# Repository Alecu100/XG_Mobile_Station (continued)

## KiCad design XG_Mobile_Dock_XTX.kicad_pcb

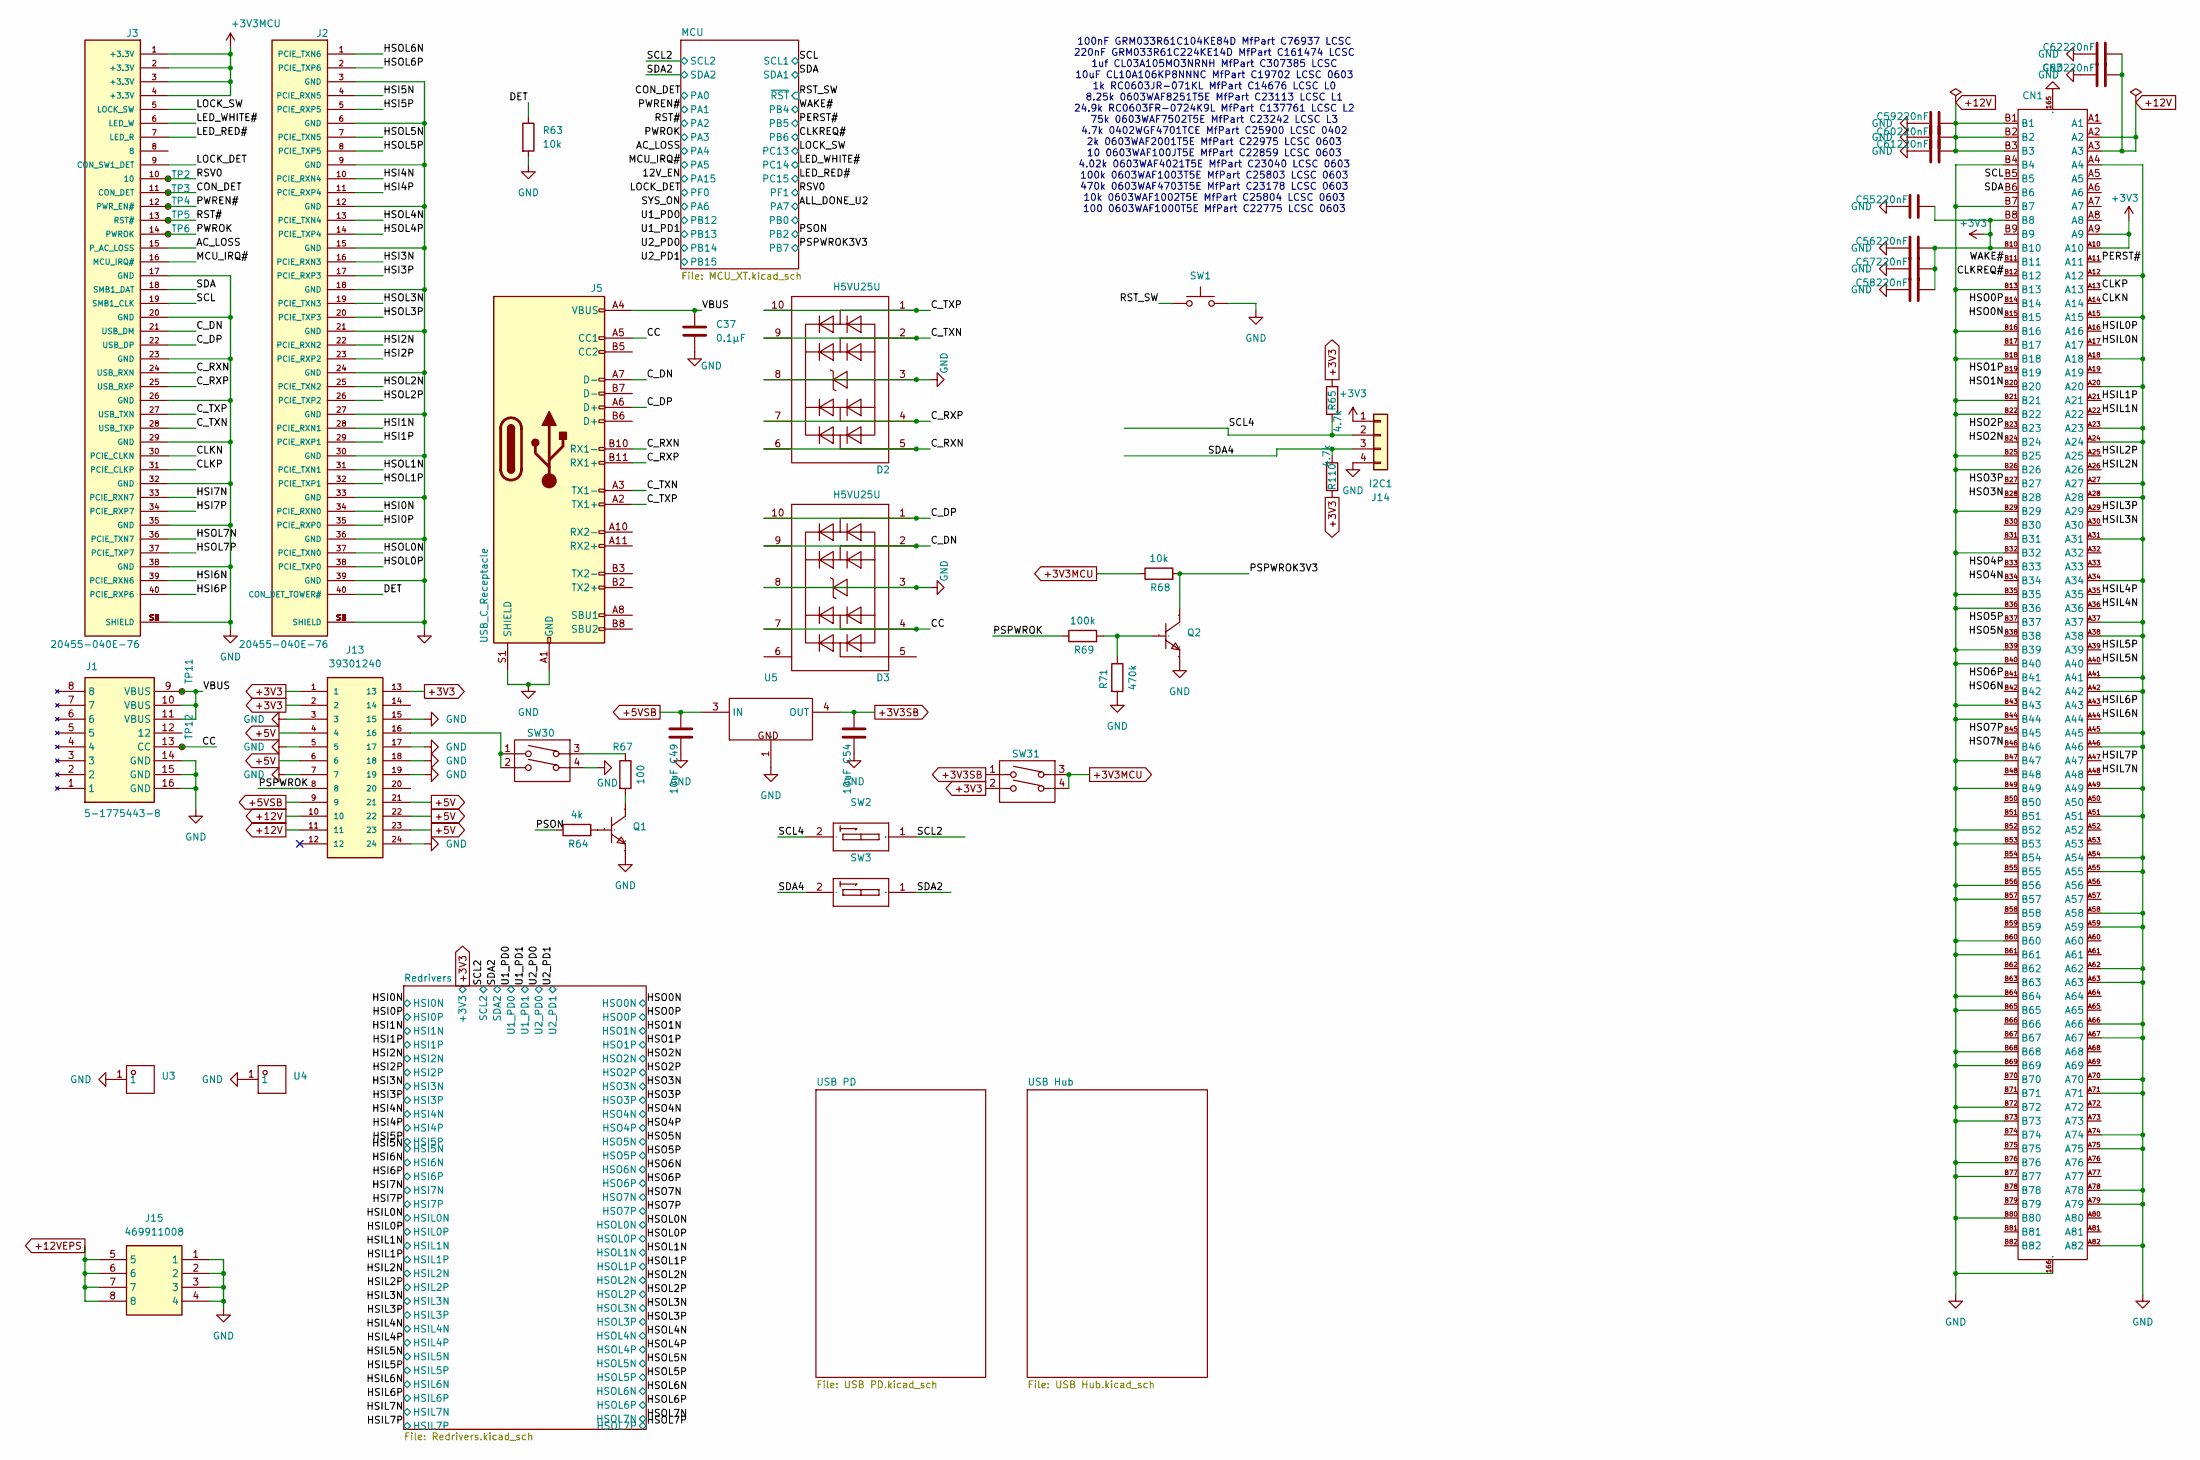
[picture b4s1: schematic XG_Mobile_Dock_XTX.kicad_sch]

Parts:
C37: 0.1μF; C_0402_1005Metric; Part_Number CL05B104KO5NNNC; LCSC C1525
C49, C54: 10uF; C_0603_1608Metric; Part_Number CL10A106KP8NNNC; LCSC C19702
C55, C56, C57, C58, C59, C60, C61, C62, C63: 220nF; C_0201_0603Metric; Part_Number GRM033R61C224KE14D; LCSC C161474
CN1: CONN-SMD_164P-P1.00_2EH5827-D29BN-3H; Part_Number 21650-11013T; LCSC C22464457
D2, D3: H5VU25U; AZ1045-04F; Part_Number H5VU25U; LCSC C7420374
J1: 5-1775443-8; Manufacturer_Part_Number 5-1775443-8
J2, J3: 20455-040E-76; Part_Number 20455-040E-76; LCSC C5160883
J5: USB_C_Receptacle; USB-C-SMD_TYPE-C-24P-QT; Part_Number TYPE-C 24P QT; LCSC C2681555
J13: 39301240; CON_39300240; Part_Number 39301240; LCSC C492347
J14: I2C1; PinHeader_1x04_P2.54mm_Vertical; Part_Number 2.54-1*4; LCSC C5116483
J15: 469911008; CON_469911008; Part_Number 469911008; LCSC C17470577
Q1, Q2: SOT-23-3_L2.9-W1.3-P1.90-LS2.4-BR; Part_Number MMBT5551(RANGE:200-300); LCSC C2145
R63: 10k; R_0402_1005Metric; Part_Number 0402WGF1002TCE; LCSC C25744
R64: 4k; R_0603_1608Metric; Part_Number 0603WAF4021T5E; LCSC C23040
R65, R110: 4.7k; R_0402_1005Metric; Part_Number 0402WGF4701TCE; LCSC C25900
R67: 100; R_0603_1608Metric; Part_Number 0603WAF1000T5E; LCSC C22775
R68: 10k; R_0603_1608Metric; Part_Number 0603WAF1002T5E; LCSC C25804
R69: 100k; R_0603_1608Metric; Part_Number 0603WAF1003T5E; LCSC C25803
R71: 470k; R_0603_1608Metric; Part_Number 0603WAF4703T5E; LCSC C23178
SW1: SW_Push; SW_SPST_SKQG_WithStem; Part_Number TS-1187A-B-A-B; LCSC C318884
SW2, SW3: SW-TH_DSWB01LHGET; Part_Number DSWB01LHGET; LCSC Part Name 红色宽体1位顶拨插件
SW30, SW31: SW-TH_DSWB02LHGET; Part_Number DSWB02LHGET; LCSC C99421
TP2, TP3, TP4, TP5, TP6, TP11, TP12: TestPoint_Small; TestPoint_Pad_D1.0mm
U3, U4: CONN-SMD_T31000; Part_Number T31000; LCSC C481468
U5: TO-252-2_L6.5-W6.1-P4.58-LS10.0-TL; Part_Number LD1086DT33TR; LCSC C12051

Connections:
+3V3SB: C54.2, SW31.1, U5.4 (OUT)
+5V: J13.4, J13.6, J13.21, J13.22, J13.23
+5VSB: C49.2, J13.9, U5.3 (IN)
+12V: C59.1, C60.1, C61.1, C62.1, C63.1, CN1.A2, CN1.A3, CN1.B1, CN1.B2, CN1.B3, J13.10, J13.11; also elsewhere on the board
+12VEPS: J15.5, J15.6, J15.7, J15.8
/AC_LOSS: J3.15 (P_AC_LOSS); also elsewhere on the board
/CC: D3.4 (I/O_3), D3.7 (NC), J1.13 (CC), J5.A5 (CC1), TP12.1
/CLKN: CN1.A14, J3.30 (PCIE_CLKN)
/CLKP: CN1.A13, J3.31 (PCIE_CLKP)
/CLKREQ#: CN1.B12; also elsewhere on the board
/CON_DET: J3.11 (CON_DET), TP3.1; also elsewhere on the board
/C_DN: D3.2 (I/O_2), D3.9 (NC), J3.21 (USB_DM), J5.A7 (D-)
/C_DP: D3.1 (I/O_1), D3.10 (NC), J3.22 (USB_DP), J5.A6 (D+)
/C_RXN: D2.5 (I/O_4), D2.6 (NC), J3.24 (USB_RXN), J5.B10 (RX1-)
/C_RXP: D2.4 (I/O_3), D2.7 (NC), J3.25 (USB_RXP), J5.B11 (RX1+)
/C_TXN: D2.2 (I/O_2), D2.9 (NC), J3.28 (USB_TXP), J5.A3 (TX1-)
/C_TXP: D2.1 (I/O_1), D2.10 (NC), J3.27 (USB_TXN), J5.A2 (TX1+)
/DET: J2.40 (CON_DET_TOWER#), R63.1
/HSI0N: J2.34 (PCIE_RXN0); also elsewhere on the board
/HSI0P: J2.35 (PCIE_RXP0); also elsewhere on the board
/HSI1N: J2.28 (PCIE_RXN1); also elsewhere on the board
/HSI1P: J2.29 (PCIE_RXP1); also elsewhere on the board
/HSI2N: J2.22 (PCIE_RXN2); also elsewhere on the board
/HSI2P: J2.23 (PCIE_RXP2); also elsewhere on the board
/HSI3N: J2.16 (PCIE_RXN3); also elsewhere on the board
/HSI3P: J2.17 (PCIE_RXP3); also elsewhere on the board
/HSI4N: J2.10 (PCIE_RXN4); also elsewhere on the board
/HSI4P: J2.11 (PCIE_RXP4); also elsewhere on the board
/HSI5N: J2.4 (PCIE_RXN5); also elsewhere on the board
/HSI5P: J2.5 (PCIE_RXP5); also elsewhere on the board
/HSI6N: J3.39 (PCIE_RXN6); also elsewhere on the board
/HSI6P: J3.40 (PCIE_RXP6); also elsewhere on the board
/HSI7N: J3.33 (PCIE_RXN7); also elsewhere on the board
/HSI7P: J3.34 (PCIE_RXP7); also elsewhere on the board
/HSIL0N: CN1.A17; also elsewhere on the board
/HSIL0P: CN1.A16; also elsewhere on the board
/HSIL1N: CN1.A22; also elsewhere on the board
/HSIL1P: CN1.A21; also elsewhere on the board
/HSIL2N: CN1.A26; also elsewhere on the board
/HSIL2P: CN1.A25; also elsewhere on the board
/HSIL3N: CN1.A30; also elsewhere on the board
/HSIL3P: CN1.A29; also elsewhere on the board
/HSIL4N: CN1.A36; also elsewhere on the board
/HSIL4P: CN1.A35; also elsewhere on the board
/HSIL5N: CN1.A40; also elsewhere on the board
/HSIL5P: CN1.A39; also elsewhere on the board
/HSIL6N: CN1.A44; also elsewhere on the board
/HSIL6P: CN1.A43; also elsewhere on the board
/HSIL7N: CN1.A48; also elsewhere on the board
/HSIL7P: CN1.A47; also elsewhere on the board
/HSO0N: CN1.B15; also elsewhere on the board
/HSO0P: CN1.B14; also elsewhere on the board
/HSO1N: CN1.B20; also elsewhere on the board
/HSO1P: CN1.B19; also elsewhere on the board
/HSO2N: CN1.B24; also elsewhere on the board
/HSO2P: CN1.B23; also elsewhere on the board
/HSO3N: CN1.B28; also elsewhere on the board
/HSO3P: CN1.B27; also elsewhere on the board
/HSO4N: CN1.B34; also elsewhere on the board
/HSO4P: CN1.B33; also elsewhere on the board
/HSO5N: CN1.B38; also elsewhere on the board
/HSO5P: CN1.B37; also elsewhere on the board
/HSO6N: CN1.B42; also elsewhere on the board
/HSO6P: CN1.B41; also elsewhere on the board
/HSO7N: CN1.B46; also elsewhere on the board
/HSO7P: CN1.B45; also elsewhere on the board
/HSOL0N: J2.37 (PCIE_TXN0); also elsewhere on the board
/HSOL0P: J2.38 (PCIE_TXP0); also elsewhere on the board
/HSOL1N: J2.31 (PCIE_TXN1); also elsewhere on the board
/HSOL1P: J2.32 (PCIE_TXP1); also elsewhere on the board
/HSOL2N: J2.25 (PCIE_TXN2); also elsewhere on the board
/HSOL2P: J2.26 (PCIE_TXP2); also elsewhere on the board
/HSOL3N: J2.19 (PCIE_TXN3); also elsewhere on the board
/HSOL3P: J2.20 (PCIE_TXP3); also elsewhere on the board
/HSOL4N: J2.13 (PCIE_TXN4); also elsewhere on the board
/HSOL4P: J2.14 (PCIE_TXP4); also elsewhere on the board
/HSOL5N: J2.7 (PCIE_TXN5); also elsewhere on the board
/HSOL5P: J2.8 (PCIE_TXP5); also elsewhere on the board
/HSOL6N: J2.1 (PCIE_TXN6); also elsewhere on the board
/HSOL6P: J2.2 (PCIE_TXP6); also elsewhere on the board
/HSOL7N: J3.36 (PCIE_TXN7); also elsewhere on the board
/HSOL7P: J3.37 (PCIE_TXP7); also elsewhere on the board
/LED_RED#: J3.7 (LED_R); also elsewhere on the board
/LED_WHITE#: J3.6 (LED_W); also elsewhere on the board
/LOCK_DET: J3.9 (CON_SW1_DET); also elsewhere on the board
/LOCK_SW: J3.5 (LOCK_SW); also elsewhere on the board
/MCU_IRQ#: J3.16 (MCU_IRQ#); also elsewhere on the board
/PERST#: CN1.A11; also elsewhere on the board
/PSON: R64.1; also elsewhere on the board
/PSPWROK: J13.8, R69.1
/PSPWROK3V3: Q2.3 (C), R68.2; also elsewhere on the board
/PWREN#: J3.12 (PWR_EN#), TP4.1; also elsewhere on the board
/PWROK: J3.14 (PWROK), TP6.1; also elsewhere on the board
/RST#: J3.13 (RST#), TP5.1; also elsewhere on the board
/RST_SW: SW1.1; also elsewhere on the board
/RSV0: J3.10, TP2.1; also elsewhere on the board
/SCL: CN1.B5, J3.19 (SMB1_CLK); also elsewhere on the board
/SCL2: SW2.1 (A1); also elsewhere on the board
/SCL4: J14.2, R65.1, SW2.2
/SDA: CN1.B6, J3.18 (SMB1_DAT); also elsewhere on the board
/SDA2: SW3.1 (A1); also elsewhere on the board
/SDA4: J14.3, R110.1, SW3.2
/VBUS: C37.1, J1.9 (VBUS), J1.10 (VBUS), J1.11 (VBUS), J5.A4 (VBUS), J5.A9 (VBUS), J5.B4 (VBUS), J5.B9 (VBUS), TP11.1
/WAKE#: CN1.B11; also elsewhere on the board
GND: C37.2, C49.1, C54.1, C55.2, C56.2, C57.2, C58.2, C59.2, C60.2, C61.2, C62.2, C63.2, CN1.165, CN1.166, CN1.A4, CN1.A12, CN1.A15, CN1.A18, CN1.A20, CN1.A23, CN1.A24, CN1.A27, CN1.A28, CN1.A31, CN1.A34, CN1.A37, CN1.A38, CN1.A41, CN1.A42, CN1.A45, CN1.A46, CN1.A49, CN1.A51, CN1.A54, CN1.A55, CN1.A58, CN1.A59, CN1.A62, CN1.A63, CN1.A66, CN1.A67, CN1.A70, CN1.A71, CN1.A74, CN1.A75, CN1.A78, CN1.A79, CN1.A82, CN1.B4, CN1.B7, CN1.B13, CN1.B16, CN1.B18, CN1.B21, CN1.B22, CN1.B25, CN1.B26, CN1.B29, CN1.B32, CN1.B35, CN1.B36, CN1.B39, CN1.B40, CN1.B43, CN1.B44, CN1.B47, CN1.B49, CN1.B52, CN1.B53, CN1.B56, CN1.B57, CN1.B60, CN1.B61, CN1.B64, CN1.B65, CN1.B68, CN1.B69, CN1.B72, CN1.B73, CN1.B76, CN1.B77, CN1.B80, D2.3 (GND), D2.8 (GND), D3.3 (GND), D3.8 (GND), J1.14 (GND), J1.15 (GND), J1.16 (GND), J2.3 (GND), J2.6 (GND), J2.9 (GND), J2.12 (GND), J2.15 (GND), J2.18 (GND), J2.21 (GND), J2.24 (GND), J2.27 (GND), J2.30 (GND), J2.33 (GND), J2.36 (GND), J2.39 (GND), J2.S1 (SHIELD), J2.S2 (SHIELD), J2.S3 (SHIELD), J2.S4 (SHIELD), J3.17 (GND), J3.20 (GND), J3.23 (GND), J3.26 (GND), J3.29 (GND), J3.32 (GND), J3.35 (GND), J3.38 (GND), J3.S1 (SHIELD), J3.S2 (SHIELD), J3.S3 (SHIELD), J3.S4 (SHIELD), J5.A1 (GND), J5.A12 (GND), J5.B1 (GND), J5.B12 (GND), J5.S1 (SHIELD), J13.3, J13.5, J13.7, J13.15, J13.17, J13.18, J13.19, J13.24, J14.4, J15.1, J15.2, J15.3, J15.4, Q1.2 (E), Q2.2 (E), R63.2, R71.2, SW1.2, SW30.4, U3.1, U4.1, U5.1 (GND); also elsewhere on the board
unnamed: J13.16, SW30.1, SW30.2
unnamed: Q1.1 (B), R64.2
unnamed: Q1.3 (C), R67.2
unnamed: Q2.1 (B), R69.2, R71.1
unnamed: R67.1, SW30.3

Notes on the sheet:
100nF GRM033R61C104KE84D MfPart C76937 LCSC 220nF GRM033R61C224KE14D MfPart C161474 LCSC 1uf CL03A105MO3NRNH MfPart C307385 LCSC 10uF CL10A106KP8NNNC MfPart C19702 LCSC 0603 1k RC0603JR-071KL MfPart C14676 LCSC L0 8.25k 0603WAF8251T5E MfPart C23113 LCSC L1 24.9k RC0603FR-0724K9L MfPart C137761 LCSC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

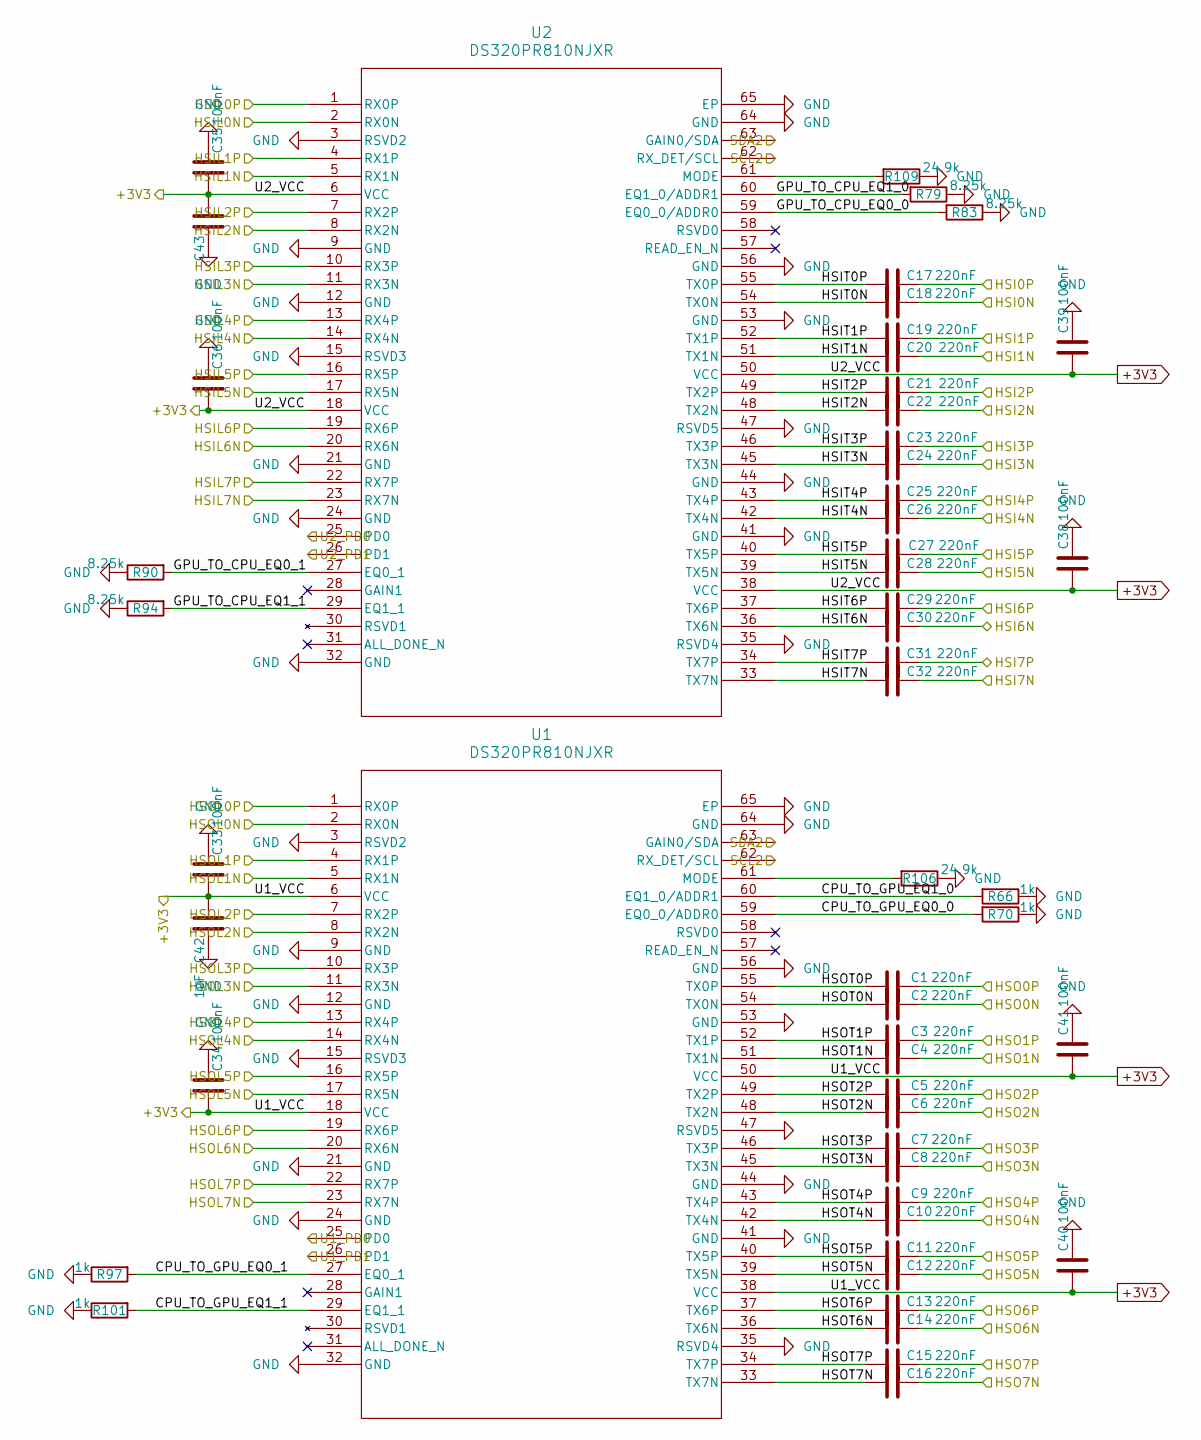
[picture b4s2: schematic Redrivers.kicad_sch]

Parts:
C1, C2, C3, C4, C5, C6, C7, C8, C9, C10, C11, C12, C13, C14, C15, C16, C17, C18, C19, C20, C21, C22, C23, C24, C25, C26, C27, C28, C29, C30, C31, C32: 220nF; C_0201_0603Metric; Part_Number GRM033R61C224KE14D; LCSC C161474
C33, C34, C35, C36, C38, C39, C40, C41: 100nF; C_0201_0603Metric; Part_Number GRM033R61C104KE84D; LCSC C76937
C42, C43: 1uF; C_0201_0603Metric; Part_Number CL03A105MO3NRNH; LCSC C307385
R66, R70, R97, R101: 1k; R_0603_1608Metric; Part_Number RC0603JR-071KL; LCSC C14676
R79, R83, R90, R94: 8.25k; R_0603_1608Metric; Part_Number 0603WAF8251T5E; LCSC C23113
R106, R109: 24.9k; R_0603_1608Metric; Part_Number RC0603FR-0724K9L; LCSC C137761
U1, U2: DS320PR810NJXR; WQFN-64-NJX_TEX; Part_Number DS320PR810NJXR; LCSC C6539577

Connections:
/HSI0N: C18.1; also elsewhere on the board
/HSI0P: C17.1; also elsewhere on the board
/HSI1N: C20.1; also elsewhere on the board
/HSI1P: C19.1; also elsewhere on the board
/HSI2N: C22.1; also elsewhere on the board
/HSI2P: C21.1; also elsewhere on the board
/HSI3N: C24.1; also elsewhere on the board
/HSI3P: C23.1; also elsewhere on the board
/HSI4N: C26.1; also elsewhere on the board
/HSI4P: C25.1; also elsewhere on the board
/HSI5N: C28.1; also elsewhere on the board
/HSI5P: C27.1; also elsewhere on the board
/HSI6N: C30.1; also elsewhere on the board
/HSI6P: C29.1; also elsewhere on the board
/HSI7N: C32.1; also elsewhere on the board
/HSI7P: C31.1; also elsewhere on the board
/HSIL0N: U2.2 (RX0N); also elsewhere on the board
/HSIL0P: U2.1 (RX0P); also elsewhere on the board
/HSIL1N: U2.5 (RX1N); also elsewhere on the board
/HSIL1P: U2.4 (RX1P); also elsewhere on the board
/HSIL2N: U2.8 (RX2N); also elsewhere on the board
/HSIL2P: U2.7 (RX2P); also elsewhere on the board
/HSIL3N: U2.11 (RX3N); also elsewhere on the board
/HSIL3P: U2.10 (RX3P); also elsewhere on the board
/HSIL4N: U2.14 (RX4N); also elsewhere on the board
/HSIL4P: U2.13 (RX4P); also elsewhere on the board
/HSIL5N: U2.17 (RX5N); also elsewhere on the board
/HSIL5P: U2.16 (RX5P); also elsewhere on the board
/HSIL6N: U2.20 (RX6N); also elsewhere on the board
/HSIL6P: U2.19 (RX6P); also elsewhere on the board
/HSIL7N: U2.23 (RX7N); also elsewhere on the board
/HSIL7P: U2.22 (RX7P); also elsewhere on the board
/HSO0N: C2.1; also elsewhere on the board
/HSO0P: C1.1; also elsewhere on the board
/HSO1N: C4.1; also elsewhere on the board
/HSO1P: C3.1; also elsewhere on the board
/HSO2N: C6.1; also elsewhere on the board
/HSO2P: C5.1; also elsewhere on the board
/HSO3N: C8.1; also elsewhere on the board
/HSO3P: C7.1; also elsewhere on the board
/HSO4N: C10.1; also elsewhere on the board
/HSO4P: C9.1; also elsewhere on the board
/HSO5N: C12.1; also elsewhere on the board
/HSO5P: C11.1; also elsewhere on the board
/HSO6N: C14.1; also elsewhere on the board
/HSO6P: C13.1; also elsewhere on the board
/HSO7N: C16.1; also elsewhere on the board
/HSO7P: C15.1; also elsewhere on the board
/HSOL0N: U1.2 (RX0N); also elsewhere on the board
/HSOL0P: U1.1 (RX0P); also elsewhere on the board
/HSOL1N: U1.5 (RX1N); also elsewhere on the board
/HSOL1P: U1.4 (RX1P); also elsewhere on the board
/HSOL2N: U1.8 (RX2N); also elsewhere on the board
/HSOL2P: U1.7 (RX2P); also elsewhere on the board
/HSOL3N: U1.11 (RX3N); also elsewhere on the board
/HSOL3P: U1.10 (RX3P); also elsewhere on the board
/HSOL4N: U1.14 (RX4N); also elsewhere on the board
/HSOL4P: U1.13 (RX4P); also elsewhere on the board
/HSOL5N: U1.17 (RX5N); also elsewhere on the board
/HSOL5P: U1.16 (RX5P); also elsewhere on the board
/HSOL6N: U1.20 (RX6N); also elsewhere on the board
/HSOL6P: U1.19 (RX6P); also elsewhere on the board
/HSOL7N: U1.23 (RX7N); also elsewhere on the board
/HSOL7P: U1.22 (RX7P); also elsewhere on the board
/Redrivers/CPU_TO_GPU_EQ0_0: R70.2, U1.59 (EQ0_0/ADDR0)
/Redrivers/CPU_TO_GPU_EQ0_1: R97.2, U1.27 (EQ0_1)
/Redrivers/CPU_TO_GPU_EQ1_0: R66.2, U1.60 (EQ1_0/ADDR1)
/Redrivers/CPU_TO_GPU_EQ1_1: R101.2, U1.29 (EQ1_1)
/Redrivers/GPU_TO_CPU_EQ0_0: R83.2, U2.59 (EQ0_0/ADDR0)
/Redrivers/GPU_TO_CPU_EQ0_1: R90.2, U2.27 (EQ0_1)
/Redrivers/GPU_TO_CPU_EQ1_0: R79.2, U2.60 (EQ1_0/ADDR1)
/Redrivers/GPU_TO_CPU_EQ1_1: R94.2, U2.29 (EQ1_1)
/Redrivers/HSIT0N: C18.2, U2.54 (TX0N)
/Redrivers/HSIT0P: C17.2, U2.55 (TX0P)
/Redrivers/HSIT1N: C20.2, U2.51 (TX1N)
/Redrivers/HSIT1P: C19.2, U2.52 (TX1P)
/Redrivers/HSIT2N: C22.2, U2.48 (TX2N)
/Redrivers/HSIT2P: C21.2, U2.49 (TX2P)
/Redrivers/HSIT3N: C24.2, U2.45 (TX3N)
/Redrivers/HSIT3P: C23.2, U2.46 (TX3P)
/Redrivers/HSIT4N: C26.2, U2.42 (TX4N)
/Redrivers/HSIT4P: C25.2, U2.43 (TX4P)
/Redrivers/HSIT5N: C28.2, U2.39 (TX5N)
/Redrivers/HSIT5P: C27.2, U2.40 (TX5P)
/Redrivers/HSIT6N: C30.2, U2.36 (TX6N)
/Redrivers/HSIT6P: C29.2, U2.37 (TX6P)
/Redrivers/HSIT7N: C32.2, U2.33 (TX7N)
/Redrivers/HSIT7P: C31.2, U2.34 (TX7P)
/Redrivers/HSOT0N: C2.2, U1.54 (TX0N)
/Redrivers/HSOT0P: C1.2, U1.55 (TX0P)
/Redrivers/HSOT1N: C4.2, U1.51 (TX1N)
/Redrivers/HSOT1P: C3.2, U1.52 (TX1P)
/Redrivers/HSOT2N: C6.2, U1.48 (TX2N)
/Redrivers/HSOT2P: C5.2, U1.49 (TX2P)
/Redrivers/HSOT3N: C8.2, U1.45 (TX3N)
/Redrivers/HSOT3P: C7.2, U1.46 (TX3P)
/Redrivers/HSOT4N: C10.2, U1.42 (TX4N)
/Redrivers/HSOT4P: C9.2, U1.43 (TX4P)
/Redrivers/HSOT5N: C12.2, U1.39 (TX5N)
/Redrivers/HSOT5P: C11.2, U1.40 (TX5P)
/Redrivers/HSOT6N: C14.2, U1.36 (TX6N)
/Redrivers/HSOT6P: C13.2, U1.37 (TX6P)
/Redrivers/HSOT7N: C16.2, U1.33 (TX7N)
/Redrivers/HSOT7P: C15.2, U1.34 (TX7P)
/SCL2: U1.62 (RX_DET/SCL), U2.62 (RX_DET/SCL); also elsewhere on the board
/SDA2: U1.63 (GAIN0/SDA), U2.63 (GAIN0/SDA); also elsewhere on the board
/U1_PD0: U1.25 (PD0); also elsewhere on the board
/U1_PD1: U1.26 (PD1); also elsewhere on the board
/U2_PD0: U2.25 (PD0); also elsewhere on the board
/U2_PD1: U2.26 (PD1); also elsewhere on the board
GND: C33.1, C34.1, C35.1, C36.1, C38.1, C39.1, C40.1, C41.1, C42.1, C43.1, R66.1, R70.1, R79.1, R83.1, R90.1, R94.1, R97.1, R101.1, R106.1, R109.1, U1.3 (RSVD2), U1.9 (GND), U1.12 (GND), U1.15 (RSVD3), U1.21 (GND), U1.24 (GND), U1.32 (GND), U1.35 (RSVD4), U1.41 (GND), U1.44 (GND), U1.47 (RSVD5), U1.53 (GND), U1.56 (GND), U1.64 (GND), U1.65 (EP), U2.3 (RSVD2), U2.9 (GND), U2.12 (GND), U2.15 (RSVD3), U2.21 (GND), U2.24 (GND), U2.32 (GND), U2.35 (RSVD4), U2.41 (GND), U2.44 (GND), U2.47 (RSVD5), U2.53 (GND), U2.56 (GND), U2.64 (GND), U2.65 (EP); also elsewhere on the board
unnamed: R106.2, U1.61 (MODE)
unnamed: R109.2, U2.61 (MODE)

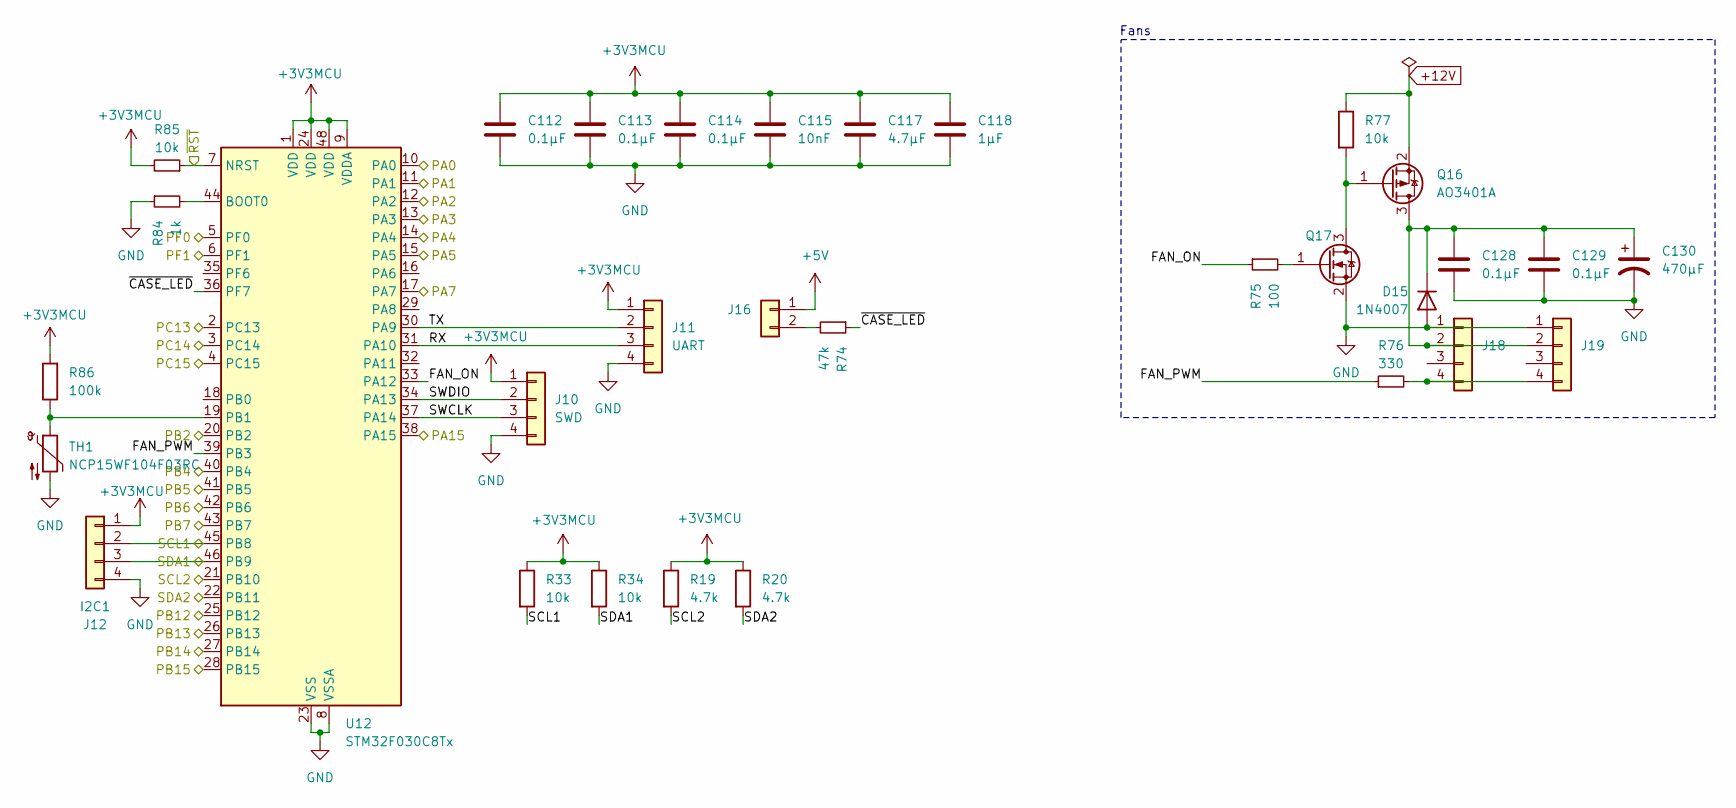
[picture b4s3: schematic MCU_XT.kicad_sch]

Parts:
C112, C113, C114: 0.1µF; C_0402_1005Metric; Part_Number CL05B104KB54PNC; LCSC C307331
C115: 10nF; C_0402_1005Metric; Part_Number CL05B103KB5NNNC; LCSC C15195
C117: 4.7µF; C_0402_1005Metric; Part_Number CL05A475MP5NRNC; LCSC C23733
C118: 1µF; C_0402_1005Metric; Part_Number CL05A105KA5NQNC; LCSC C52923
C128, C129: 0.1µF; C_0603_1608Metric; Part_Number CC0603KRX7R9BB104; LCSC C14663
C130: 470µF; CP_Radial_D10.0mm_P5.00mm; Part_Number EGT477M1HG16RRS0P; LCSC C3015599
D15: 1N4007; D_SOD-123F; Part_Number 1N4007W; LCSC C18199088
J10: SWD; PinHeader_1x04_P2.54mm_Vertical; Part_Number 2.54-1*4; LCSC C5116483
J11: UART; PinHeader_1x04_P2.54mm_Vertical; Part_Number 2.54-1*4; LCSC C5116483
J12: I2C1; PinHeader_1x04_P2.54mm_Vertical; Part_Number 2.54-1*4; LCSC C5116483
J16: JST_PH_S2B-PH-K_1x02_P2.00mm_Horizontal; Part_Number S2B-PH-KL(LF)(SN); LCSC C160237
J18, J19: CONN_SD-47053-001_H10p00_MOL; Part_Number 470531000; LCSC C240840
Q16: AO3401A; SOT-23; Part_Number AO3401A; LCSC C15127
Q17: 2N7002W; SOT-323-3_L2.0-W1.3-P1.30-LS2.1-BR; Part_Number 2N7002W; LCSC C7420322
R19, R20: 4.7k; R_0402_1005Metric; Part_Number 0402WGF4701TCE; LCSC C25900
R33, R34, R77, R85: 10k; R_0402_1005Metric; Part_Number 0402WGF1002TCE; LCSC C25744
R74: 47k; R_0402_1005Metric; Part_Number 0402WGF4702TCE; LCSC C25792
R75: 100; R_0402_1005Metric; Part_Number 0402WGF1000TCE; LCSC C25076
R76: 330; R_0402_1005Metric; Part_Number 0402WGF3300TCE; LCSC C25104
R84: 1k; R_0402_1005Metric; Part_Number 0402WGF1001TCE; LCSC C11702
R86: 100k; R_0402_1005Metric; Part_Number 0402WGF1003TCE; LCSC C25741
TH1: NCP15WF104F03RC; R_0402_1005Metric; Part_Number NCP15WF104F03RC; LCSC C77130
U12: STM32F030C8Tx; LQFP-48_7x7mm_P0.5mm; Part_Number STM32F030C8T6; LCSC C23922

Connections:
+12V: Q16.2 (S), R77.1; also elsewhere on the board
/12V_EN: U12.38 (PA15)
/AC_LOSS: U12.14 (PA4); also elsewhere on the board
/ALL_DONE_U2: U12.17 (PA7)
/CLKREQ#: U12.42 (PB6); also elsewhere on the board
/CON_DET: U12.10 (PA0); also elsewhere on the board
/LED_RED#: U12.4 (PC15); also elsewhere on the board
/LED_WHITE#: U12.3 (PC14); also elsewhere on the board
/LOCK_DET: U12.5 (PF0); also elsewhere on the board
/LOCK_SW: U12.2 (PC13); also elsewhere on the board
/MCU/FAN_ON: R75.1, U12.33 (PA12)
/MCU/FAN_PWM: R76.1, U12.39 (PB3)
/MCU/PB0: U12.18 (PB0)
/MCU/RX: J11.3, U12.31 (PA10)
/MCU/SWCLK: J10.3, U12.37 (PA14)
/MCU/SWDIO: J10.2, U12.34 (PA13)
/MCU/TX: J11.2, U12.30 (PA9)
/MCU/~CASE_LED: R74.1, U12.36 (PF7)
/MCU_IRQ#: U12.15 (PA5); also elsewhere on the board
/PERST#: U12.41 (PB5); also elsewhere on the board
/PSON: U12.20 (PB2); also elsewhere on the board
/PSPWROK3V3: U12.43 (PB7); also elsewhere on the board
/PWREN#: U12.11 (PA1); also elsewhere on the board
/PWROK: U12.13 (PA3); also elsewhere on the board
/RST#: U12.12 (PA2); also elsewhere on the board
/RST_SW: R85.1, U12.7 (NRST); also elsewhere on the board
/RSV0: U12.6 (PF1); also elsewhere on the board
/SCL: J12.2, R33.2, U12.45 (PB8); also elsewhere on the board
/SCL2: R19.2, U12.21 (PB10); also elsewhere on the board
/SDA: J12.3, R34.2, U12.46 (PB9); also elsewhere on the board
/SDA2: R20.2, U12.22 (PB11); also elsewhere on the board
/U1_PD0: U12.25 (PB12); also elsewhere on the board
/U1_PD1: U12.26 (PB13); also elsewhere on the board
/U2_PD0: U12.27 (PB14); also elsewhere on the board
/U2_PD1: U12.28 (PB15); also elsewhere on the board
/WAKE#: U12.40 (PB4); also elsewhere on the board
GND: C112.2, C113.2, C114.2, C115.2, C117.2, C118.2, C128.2, C129.2, C130.2, D15.2 (A), J10.4, J11.4, J12.4, J18.1, J19.1, Q17.2 (S), R84.1, TH1.2, U12.8 (VSSA), U12.23 (VSS), U12.47 (VSS); also elsewhere on the board
unnamed: C128.1, C129.1, C130.1, D15.1 (K), J18.2, J19.2, Q16.3 (D)
unnamed: J16.2, R74.2
unnamed: J18.4, J19.4, R76.2
unnamed: Q16.1 (G), Q17.3 (D), R77.2
unnamed: Q17.1 (G), R75.2
unnamed: R84.2, U12.44 (BOOT0)
unnamed: R86.1, TH1.1, U12.19 (PB1)

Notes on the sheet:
Fans

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
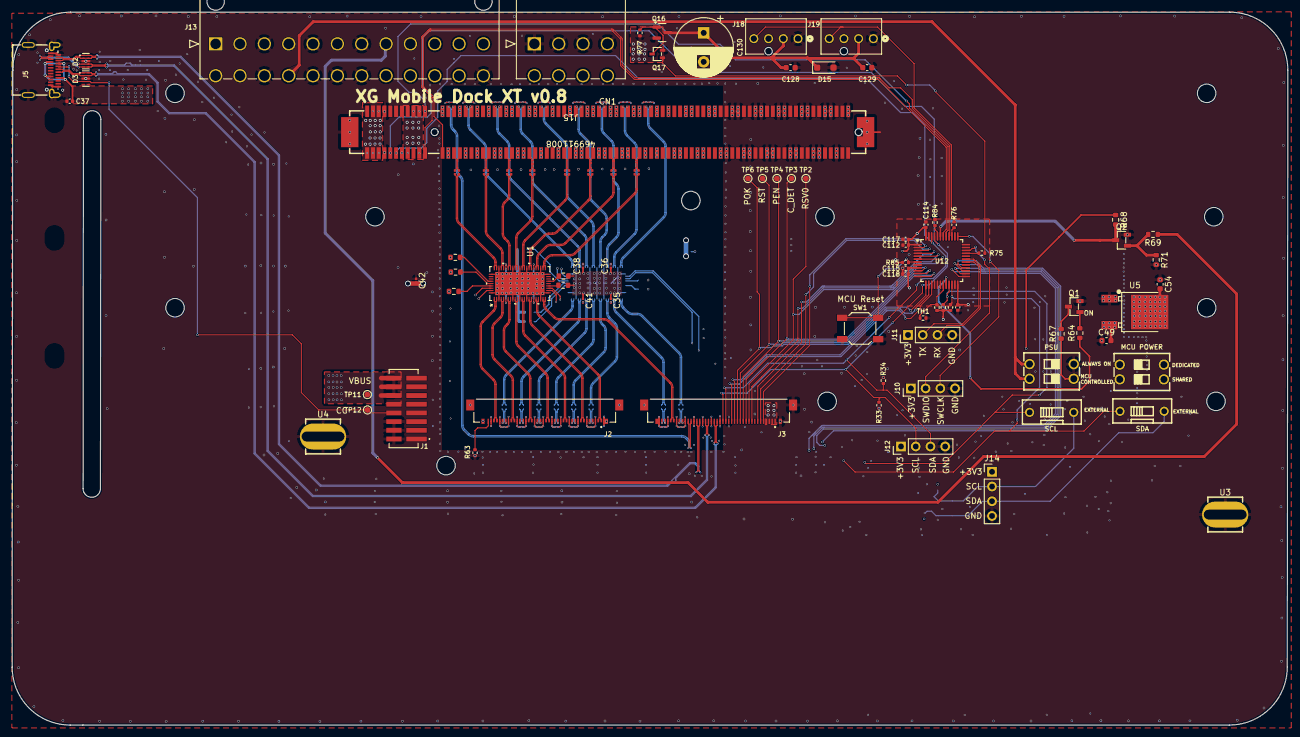
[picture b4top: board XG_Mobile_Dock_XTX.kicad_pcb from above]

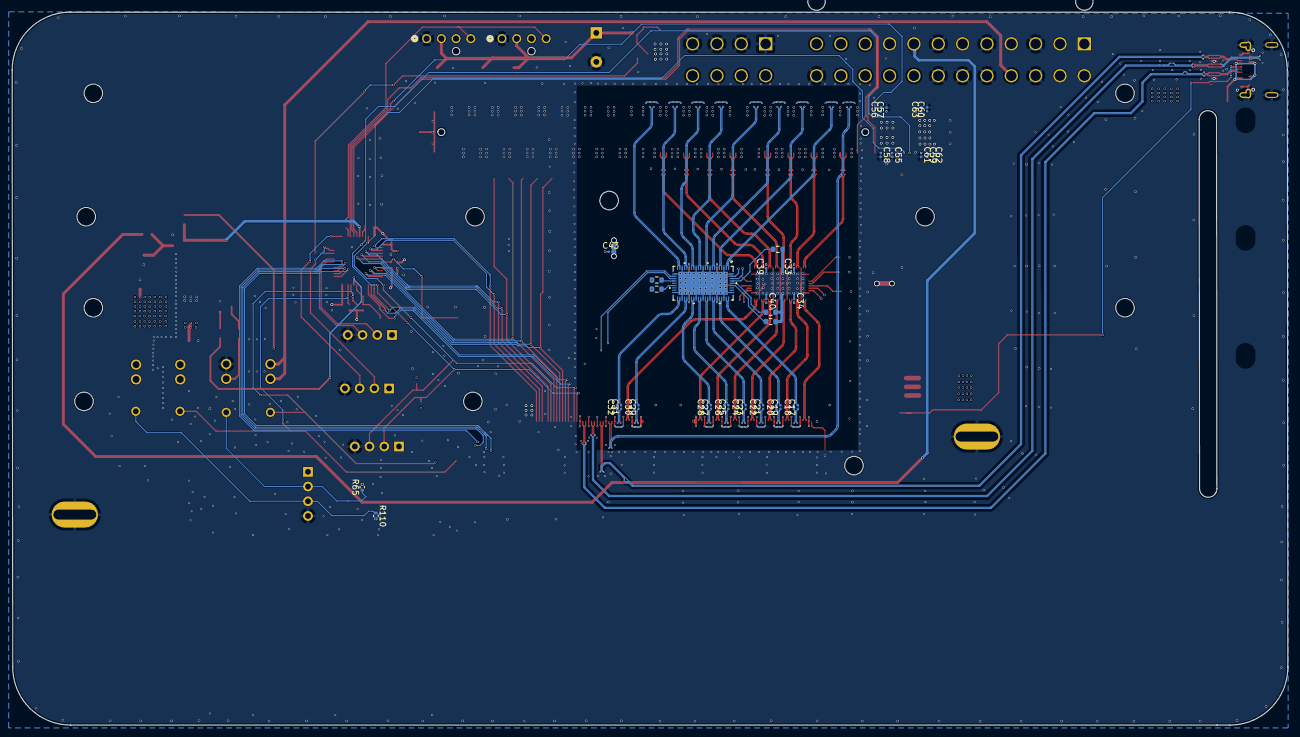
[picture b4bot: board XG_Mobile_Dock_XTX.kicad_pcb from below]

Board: 8 copper layers, 220.1 x 123.0 mm, 130 parts (38 on the bottom side), 170 nets.
